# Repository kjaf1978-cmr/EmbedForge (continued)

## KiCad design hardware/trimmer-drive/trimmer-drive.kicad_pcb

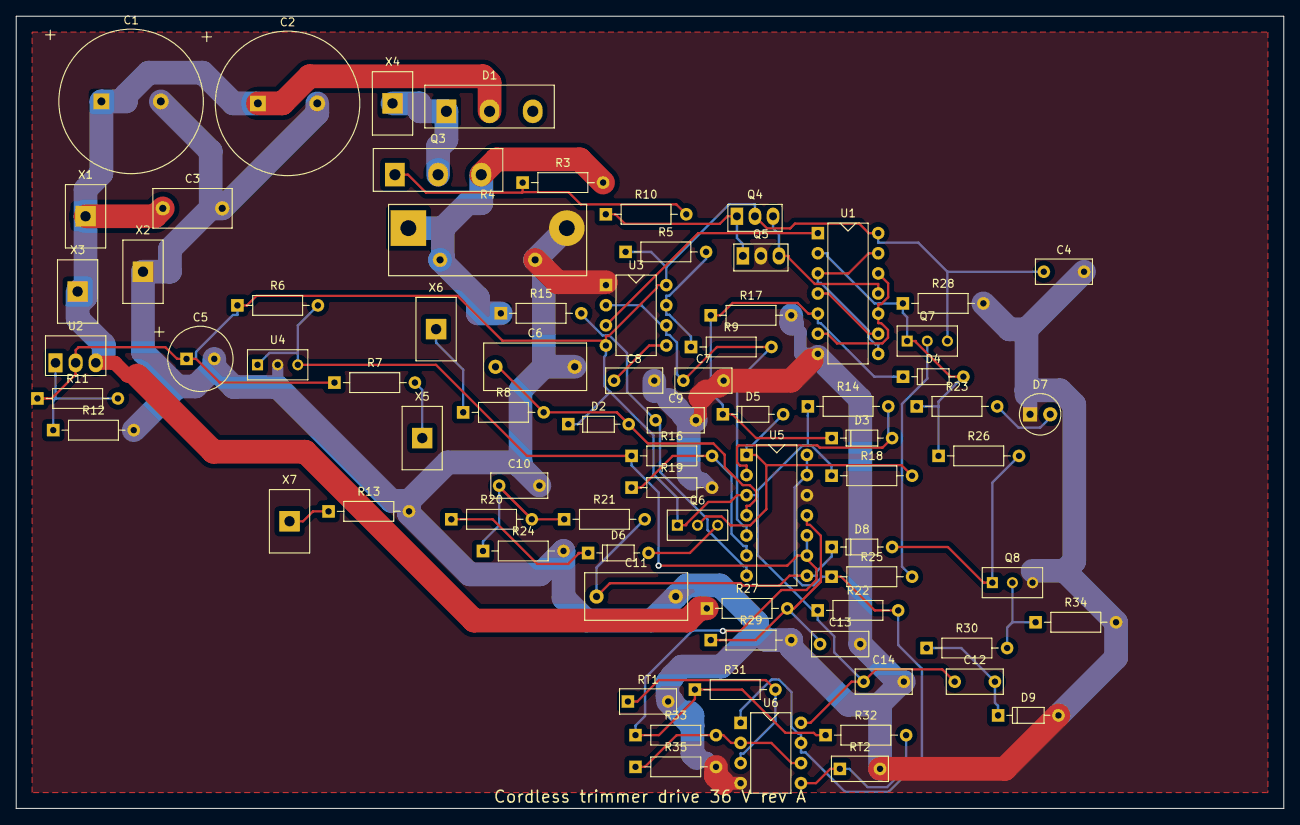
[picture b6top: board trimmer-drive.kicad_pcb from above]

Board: 2 copper layers, 160.0 x 100.0 mm, 77 parts (0 on the bottom side), 41 nets.

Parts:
C1, C2: 470u; CP_Radial_D18
C3: 1u; C_Film_P7.5
C4, C10, C14: 100n; C_Disc_5.08
C5: 47u; CP_Radial_D8
C6: 4.7u; C_Film_P10
C7, C8, C13: 10n; C_Disc_5.08
C9: 1n; C_Disc_5.08
C11: 6.8u; C_Film_P10
C12: 1u; C_Disc_5.08
D1: STTH6003; TO-247_Vertical
D2, D3, D4, D5, D6, D8, D9: 1N4148; D_DO-35
D7: red; LED_D5.0
Q3: IRFP4110; TO-247_Vertical
Q4: BD139; TO-126_Vertical
Q5: BD140; TO-126_Vertical
Q6, Q8: BC547B; TO-92_Wide
Q7: BC557B; TO-92_Wide
R3, R14, R18, R22, R25, R28, R29, R31, R32: 10k; R_Axial_0207
R4: 0.005; R_Shunt_4T
R5: 6.8k; R_Axial_0207
R6, R23: 2.2k; R_Axial_0207
R7: 3.3k; R_Axial_0207
R8, R17, R21, R27, R34: 100k; R_Axial_0207
R9: 330; R_Axial_0207
R10: 10; R_Axial_0207
R11: 240; R_Axial_0207
R12: 2.05k; R_Axial_0207
R13: 3.9k; R_Axial_0207
R15, R19, R20, R35: 1k; R_Axial_0207
R16: 11.5k; R_Axial_0207
R24: 1M; R_Axial_0207
R26: 4.7k; R_Axial_0207
R30: 47k; R_Axial_0207
R33: 9.31k; R_Axial_0207
RT1, RT2: 10k; RT_Disc_5.08
U1: V12; DIP-14
U2: LM317HV; TO-220_Vertical
U3: NE555; DIP-8
U4: TL431; TO-92_Wide
U5: LM339; DIP-14
U6: LM393; DIP-8
X1: battery + (from the trigger's main contact); TerminalBlock_1x1
X2: battery -; TerminalBlock_1x1
X3: motor +; TerminalBlock_1x1
X4: motor - (and the trigger's brake contact); TerminalBlock_1x1
X5: speed pot (trigger) top; TerminalBlock_1x1
X6: speed pot wiper; TerminalBlock_1x1
X7: speed pot bottom; TerminalBlock_1x1

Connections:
ADJ: R11.2, R12.1, U2.1
BFL: Q7.2, R25.2
BPR: Q8.2, R30.2, R34.1
CLE: D6.2, Q6.3
CLF: C10.1, R20.2, R21.1, R24.1
CLJ: D6.1, R20.1
CLK: U1.1, U3.3
CT: C7.1, R9.2, U3.2, U3.6, U5.5
CV: C8.1, U3.5
DIS: R5.2, R9.1, U3.7
DRN: D1.1, Q3.2, X4.1
DRV: Q4.3, Q5.3, U1.11
FLT: D4.2, Q7.1, R23.1, R26.1, R28.1, U1.2
FLTN: R22.2, R25.1, U5.13, U5.14, U6.1, U6.7
GD: Q4.1, Q5.1, R10.1
GM: Q3.1, R3.1, R10.2
GND: C1.2, C2.2, C3.2, C4.2, C5.2, C6.2, C7.2, C8.2, C9.2, C10.2, C11.2, C13.2, C14.2, D7.1, D9.2, Q5.2, Q8.3, R4.2, R4.4, R12.2, R13.2, R17.2, R19.2, R24.2, R28.2, R29.2, R34.2, R35.2, RT1.2, RT2.2, U1.7, U3.1, U4.2, U5.12, U6.4, X2.1
IAV: C11.1, D8.1, R21.2, U5.8
LFA: D7.2, R23.2
LTA: D8.2, Q8.1, R26.2
NTH: R31.2, RT1.1, U6.3
NTM: R32.2, RT2.1, U6.5
PH: R7.2, X5.1
PL: R13.1, X7.1
PRA: C12.2, D9.1, R30.1
Q: U1.4, U1.9
QN: U1.6, U1.10, U1.12
RCLO: D5.2, Q6.2, R18.2, U5.1
RPW: D3.2, R14.2, U5.2
RST: D3.1, D4.1, D5.1, R17.1, U1.5
SET: U1.3, U1.8, U1.13
SP: C6.1, D2.2, R8.2, U5.4
SRC: Q3.3, R3.2, R4.1, R4.3, R15.1
SRF: C9.1, R15.2, U5.7
V12: C4.1, C5.1, C12.1, C14.1, D2.1, Q4.2, Q6.1, Q7.3, R5.1, R6.1, R7.1, R11.1, R14.1, R18.1, R22.1, U1.14, U2.2, U3.4, U3.8, U5.3, U6.8
VB: C1.1, C2.1, C3.1, D1.2, R27.1, U2.3, X1.1, X3.1
VBD: C13.1, R27.2, R29.1, U5.11
VCL: R16.2, R19.1, U5.6
VOT: R33.2, R35.1, U6.2, U6.6
VREF: R6.2, R16.1, R31.1, R32.1, R33.1, U4.1, U4.3, U5.9, U5.10
WIP: R8.1, X6.1

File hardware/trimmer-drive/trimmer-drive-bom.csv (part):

"on this board","qty","references","part","value","details","footprint","MPN","maker","distributors (order numbers)","unit EUR","total EUR","price basis"
"yes","2","C1 C2","Electrolytic capacitor","470 µF","voltage rating 63 V","CP_Radial_D18","470uF 63 V 105 °C (e.g. Panasonic FC series)","Panasonic / Nichicon","any distributor (radial)","0.25","0.50","estimate"
"yes","1","C3","Capacitor","1 µF","voltage rating 100 V","C_Film_P7.5","MKT film 1uF 100 V (e.g. WIMA MKS4, TDK B32529)","WIMA / TDK","any distributor (film)","0.35","0.35","estimate"
"yes","2","C4 C14","Capacitor","100 nF","voltage rating 50 V","C_Disc_5.08","ceramic X7R or MKT 100nF 50 V, 5.08 mm","KEMET / Vishay","any distributor (5.08 mm)","0.12","0.24","estimate"
"yes","1","C5","Electrolytic capacitor","47 µF","voltage rating 25 V","CP_Radial_D8","47uF 25 V 105 °C (e.g. Panasonic FC series)","Panasonic / Nichicon","any distributor (radial)","0.10","0.10","estimate"
"yes","1","C6","Capacitor","4.7 µF","voltage rating 25 V","C_Film_P10","MKT film 4.7uF 25 V (e.g. WIMA MKS4, TDK B32529)","WIMA / TDK","any distributor (film)","0.80","0.80","estimate"
"yes","2","C7 C8","Capacitor","10 nF","voltage rating 50 V","C_Disc_5.08","C0G ceramic 10nF 50 V, 5.08 mm","KEMET / Vishay","any distributor (5.08 mm)","0.10","0.20","estimate"
"yes","1","C9","Capacitor","1 nF","voltage rating 50 V","C_Disc_5.08","C0G ceramic 1nF 50 V, 5.08 mm","KEMET / Vishay","any distributor (5.08 mm)","0.10","0.10","estimate"
"yes","1","C10","Capacitor","100 nF","voltage rating 25 V","C_Disc_5.08","ceramic X7R or MKT 100nF 25 V, 5.08 mm","KEMET / Vishay","any distributor (5.08 mm)","0.12","0.12","estimate"
"yes","1","C11","Capacitor","6.8 µF","voltage rating 16 V","C_Film_P10","MKT film 6.8uF 16 V (e.g. WIMA MKS4, TDK B32529)","WIMA / TDK","any distributor (film)","0.80","0.80","estimate"
"yes","1","C12","Capacitor","1 µF","voltage rating 25 V","C_Disc_5.08","MKT film 1uF 25 V (e.g. WIMA MKS4, TDK B32529)","WIMA / TDK","any distributor (film)","0.35","0.35","estimate"
"yes","1","C13","Capacitor","10 nF","voltage rating 16 V","C_Disc_5.08","C0G ceramic 10nF 16 V, 5.08 mm","KEMET / Vishay","any distributor (5.08 mm)","0.10","0.10","estimate"
"yes","1","D1","Diode","STTH6003","","TO-247_Vertical","STTH6003CW","STMicroelectronics","Digi-Key; RS 168-6090","2.55","2.55","live"
"yes","7","D2 D3 D4 D5 D6 D8 D9","Diode","1N4148","","D_DO-35","1N4148","various","any distributor (DO-35)","0.06","0.42","estimate"
"yes","1","D7","LED","red","","LED_D5.0","5 mm red LED, 20 mA","Kingbright (e.g. L-53ID)","any distributor (5 mm LED)","0.12","0.12","estimate"
"yes","1","Q3","N-channel MOSFET","IRFP4110","","TO-247_Vertical","IRFP4110PBF","Infineon","Mouser; Digi-Key","4.20","4.20","estimate"
"yes","1","Q4","NPN transistor","BD139","","TO-126_Vertical","BD139-16","STMicroelectronics","any distributor (TO-126)","0.45","0.45","estimate"
"yes","1","Q5","PNP transistor","BD140","","TO-126_Vertical","BD140-16","STMicroelectronics","any distributor (TO-126)","0.45","0.45","estimate"
"yes","2","Q6 Q8","NPN transistor","BC547B","","TO-92_Wide","BC547B","onsemi","any distributor (TO-92)","0.10","0.20","estimate"
"yes","1","Q7","PNP transistor","BC557B","","TO-92_Wide","BC557B","onsemi","any distributor (TO-92)","0.10","0.10","estimate"
"yes","9","R3 R14 R18 R22 R25 R28 R29 R31 R32","Resistor","10 kΩ","power rating 250 mW","R_Axial_0207","metal film 10kΩ 0.6 W, 1 %, 50 ppm/K (e.g. Vishay MBB0207)","Vishay / Yageo","any distributor (0207 1 %)","0.08","0.72","estimate"
"yes","1","R4","Resistor","5 mΩ","power rating 3 W","R_Shunt_4T","BVN-M-R001-1.0","Isabellenhütte","RS 193-0103","4.00","4.00","estimate"
"yes","1","R5","Resistor","6.8 kΩ","power rating 250 mW","R_Axial_0207","metal film 6.8kΩ 0.6 W, 1 %, 50 ppm/K (e.g. Vishay MBB0207)","Vishay / Yageo","any distributor (0207 1 %)","0.08","0.08","estimate"
"yes","2","R6 R23","Resistor","2.2 kΩ","power rating 250 mW","R_Axial_0207","metal film 2.2kΩ 0.6 W, 1 %, 50 ppm/K (e.g. Vishay MBB0207)","Vishay / Yageo","any distributor (0207 1 %)","0.08","0.16","estimate"
"yes","1","R7","Resistor","3.3 kΩ","power rating 250 mW","R_Axial_0207","metal film 3.3kΩ 0.6 W, 1 %, 50 ppm/K (e.g. Vishay MBB0207)","Vishay / Yageo","any distributor (0207 1 %)","0.08","0.08","estimate"
"yes","5","R8 R17 R21 R27 R34","Resistor","100 kΩ","power rating 250 mW","R_Axial_0207","metal film 100kΩ 0.6 W, 1 %, 50 ppm/K (e.g. Vishay MBB0207)","Vishay / Yageo","any distributor (0207 1 %)","0.08","0.40","estimate"
"yes","1","R9","Resistor","330 Ω","power rating 250 mW","R_Axial_0207","metal film 330Ω 0.6 W, 1 %, 50 ppm/K (e.g. Vishay MBB0207)","Vishay / Yageo","any distributor (0207 1 %)","0.08","0.08","estimate"
"yes","1","R10","Resistor","10 Ω","power rating 250 mW","R_Axial_0207","metal film 10Ω 0.6 W, 1 %, 50 ppm/K (e.g. Vishay MBB0207)","Vishay / Yageo","any distributor (0207 1 %)","0.08","0.08","estimate"
"yes","1","R11","Resistor","240 Ω","power rating 250 mW","R_Axial_0207","metal film 240Ω 0.6 W, 1 %, 50 ppm/K (e.g. Vishay MBB0207)","Vishay / Yageo","any distributor (0207 1 %)","0.08","0.08","estimate"
"yes","1","R12","Resistor","2.05 kΩ","power rating 250 mW","R_Axial_0207","metal film 2.05kΩ 0.6 W, 1 %, 50 ppm/K (e.g. Vishay MBB0207)","Vishay / Yageo","any distributor (0207 1 %)","0.08","0.08","estimate"
"yes","1","R13","Resistor","3.9 kΩ","power rating 250 mW","R_Axial_0207","metal film 3.9kΩ 0.6 W, 1 %, 50 ppm/K (e.g. Vishay MBB0207)","Vishay / Yageo","any distributor (0207 1 %)","0.08","0.08","estimate"
"yes","4","R15 R19 R20 R35","Resistor","1 kΩ","power rating 250 mW","R_Axial_0207","metal film 1kΩ 0.6 W, 1 %, 50 ppm/K (e.g. Vishay MBB0207)","Vishay / Yageo","any distributor (0207 1 %)","0.08","0.32","estimate"
"yes","1","R16","Resistor","11.5 kΩ","power rating 250 mW","R_Axial_0207","metal film 11.5kΩ 0.6 W, 1 %, 50 ppm/K (e.g. Vishay MBB0207)","Vishay / Yageo","any distributor (0207 1 %)","0.08","0.08","estimate"
"yes","1","R24","Resistor","1 MΩ","power rating 250 mW","R_Axial_0207","metal film 1MΩ 0.6 W, 1 %, 50 ppm/K (e.g. Vishay MBB0207)","Vishay / Yageo","any distributor (0207 1 %)","0.08","0.08","estimate"
"yes","1","R26","Resistor","4.7 kΩ","power rating 250 mW","R_Axial_0207","metal film 4.7kΩ 0.6 W, 1 %, 50 ppm/K (e.g. Vishay MBB0207)","Vishay / Yageo","any distributor (0207 1 %)","0.08","0.08","estimate"
"yes","1","R30","Resistor","47 kΩ","power rating 250 mW","R_Axial_0207","metal film 47kΩ 0.6 W, 1 %, 50 ppm/K (e.g. Vishay MBB0207)","Vishay / Yageo","any distributor (0207 1 %)","0.08","0.08","estimate"
"yes","1","R33","Resistor","9.31 kΩ","power rating 250 mW","R_Axial_0207","metal film 9.31kΩ 0.6 W, 1 %, 50 ppm/K (e.g. Vishay MBB0207)","Vishay / Yageo","any distributor (0207 1 %)","0.08","0.08","estimate"
"yes","2","RT1 RT2","NTC thermistor","10 kΩ","power rating 500 mW; sensed temperature 50 °C","RT_Disc_5.08","NTCLE100E3103JB0","Vishay","Farnell 1434160; LCSC C141588; RS 754-6645","0.47","0.94","live"
"yes","1","U1","NOR gate (4 in one package)","V12","","DIP-14","CD4001BE","Texas Instruments","any distributor (DIP-14)","0.45","0.45","estimate"
"yes","1","U2","Adjustable regulator","LM317HV","","TO-220_Vertical","LM317HVT/NOPB","Texas Instruments","Mouser 926-LM317HVT/NOPB; RS 197-7244","2.20","2.20","live"
"yes","1","U3","555 timer","NE555","","DIP-8","NE555P","Texas Instruments","any distributor (DIP-8)","0.35","0.35","estimate"
"yes","1","U4","Shunt reference","TL431","","TO-92_Wide","TL431ACLP","Texas Instruments","any distributor (TO-92)","0.30","0.30","estimate"
"yes","1","U5","Comparator (4 in one package)","LM339","","DIP-14","LM339N","Texas Instruments","any distributor (DIP-14)","0.45","0.45","estimate"
"yes","1","U6","Comparator (2 in one package)","LM393","","DIP-8","LM393P","Texas Instruments","any distributor (DIP-8)","0.40","0.40","estimate"
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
